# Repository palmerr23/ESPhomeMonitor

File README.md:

# ESPhomeMonitor
Hardware for monitoring equipment using HomeAssistant and Raspberry Pi Pico W-based ESPHome installation.

The boards described here are intended to be stacked, with the main Pico W board on top.

A 3D printable case is provided, with custom escutcheons for each input or output board type.

# Boards
+ Main: Pico W, 3 x peak reading analogue inputs (400mV - 48V), filtered PWM output.
+ Analog Input: 8 x analog inputs (3.5V - 48V) 3.81mm pluggable terminals or IDC connector.
+ Analog Input (RVR): A specialised analog input board for RVR TEX150 transmitters and TXRL/RXRL STL.
+ Digital Input: eight channels, opto-isolated or non-isolated. 3.81mm pluggable terminals or IDC connector.
+ Digital Output: eight channels, 4 x opto-isolated + 4 x relays, or non-isolated. 3.81mm pluggable terminals or IDC connector.
+ Expander Board: Second stack and additional 3.3V regulator.

The boards are designed in KiCAD. Gerbers and KiCAD source files are provided.

# Case
A modular, 3D printable case is provided.
+ Base with strain relief.
+ Mid section for additional input and output boards
+ Top section for main (Pico) board.

Each board type has a customised escutcheon panel that slots into the case, designed to be laser-cut from 2mm acrylic.

The case has a top panel with ventilation and mounting points for a SHT-40 I2C temperature and humidity sensor.

The case is joined together with 12mm tapped spacers and 15mm for the main Pico board.

Case files are in STL (body) or SVG (cover and escutcheons) format.

# Documentation and configuration 

+ Technical overview (HomeAssistant Monitoring and Control.pdf)

+ KiCAD design files and an example ESPHome configuration file for each board. 

+ HomeAssistant dashboard configuration is left to the constructor as needs will differ.

ESPHome and HomeAssistant documentation is regularly updated for both platforms:
https://www.home-assistant.io/
https://esphome.io/

The HomeAssistant community forum is a useful place to search for problem resolutions on both platforms.
https://community.home-assistant.io/

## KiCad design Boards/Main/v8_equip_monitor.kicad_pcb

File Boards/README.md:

# ESPhomeMonitor Boards

# Boards

+ Main: Pico W, 3 x peak reading analogue inputs (400mV - 48V), filtered PWM output.

+ Analog Input: 8 x analog inputs (3.5V - 48V) 3.81mm pluggable terminals or IDC connector.

+ Analog Input (RVR): A specialised analog input board for RVR TEX150 transmitters and TXRL/RXRL STL.

+ Digital Input: eight channels, opto-isolated or non-isolated. 3.81mm pluggable terminals or IDC connector.

+ Digital Output: eight channels, 4 x opto-isolated + 4 x relays, or non-isolated. 3.81mm pluggable terminals or IDC connector.

+ Expander Board: Second stack and additional 3.3V regulator.

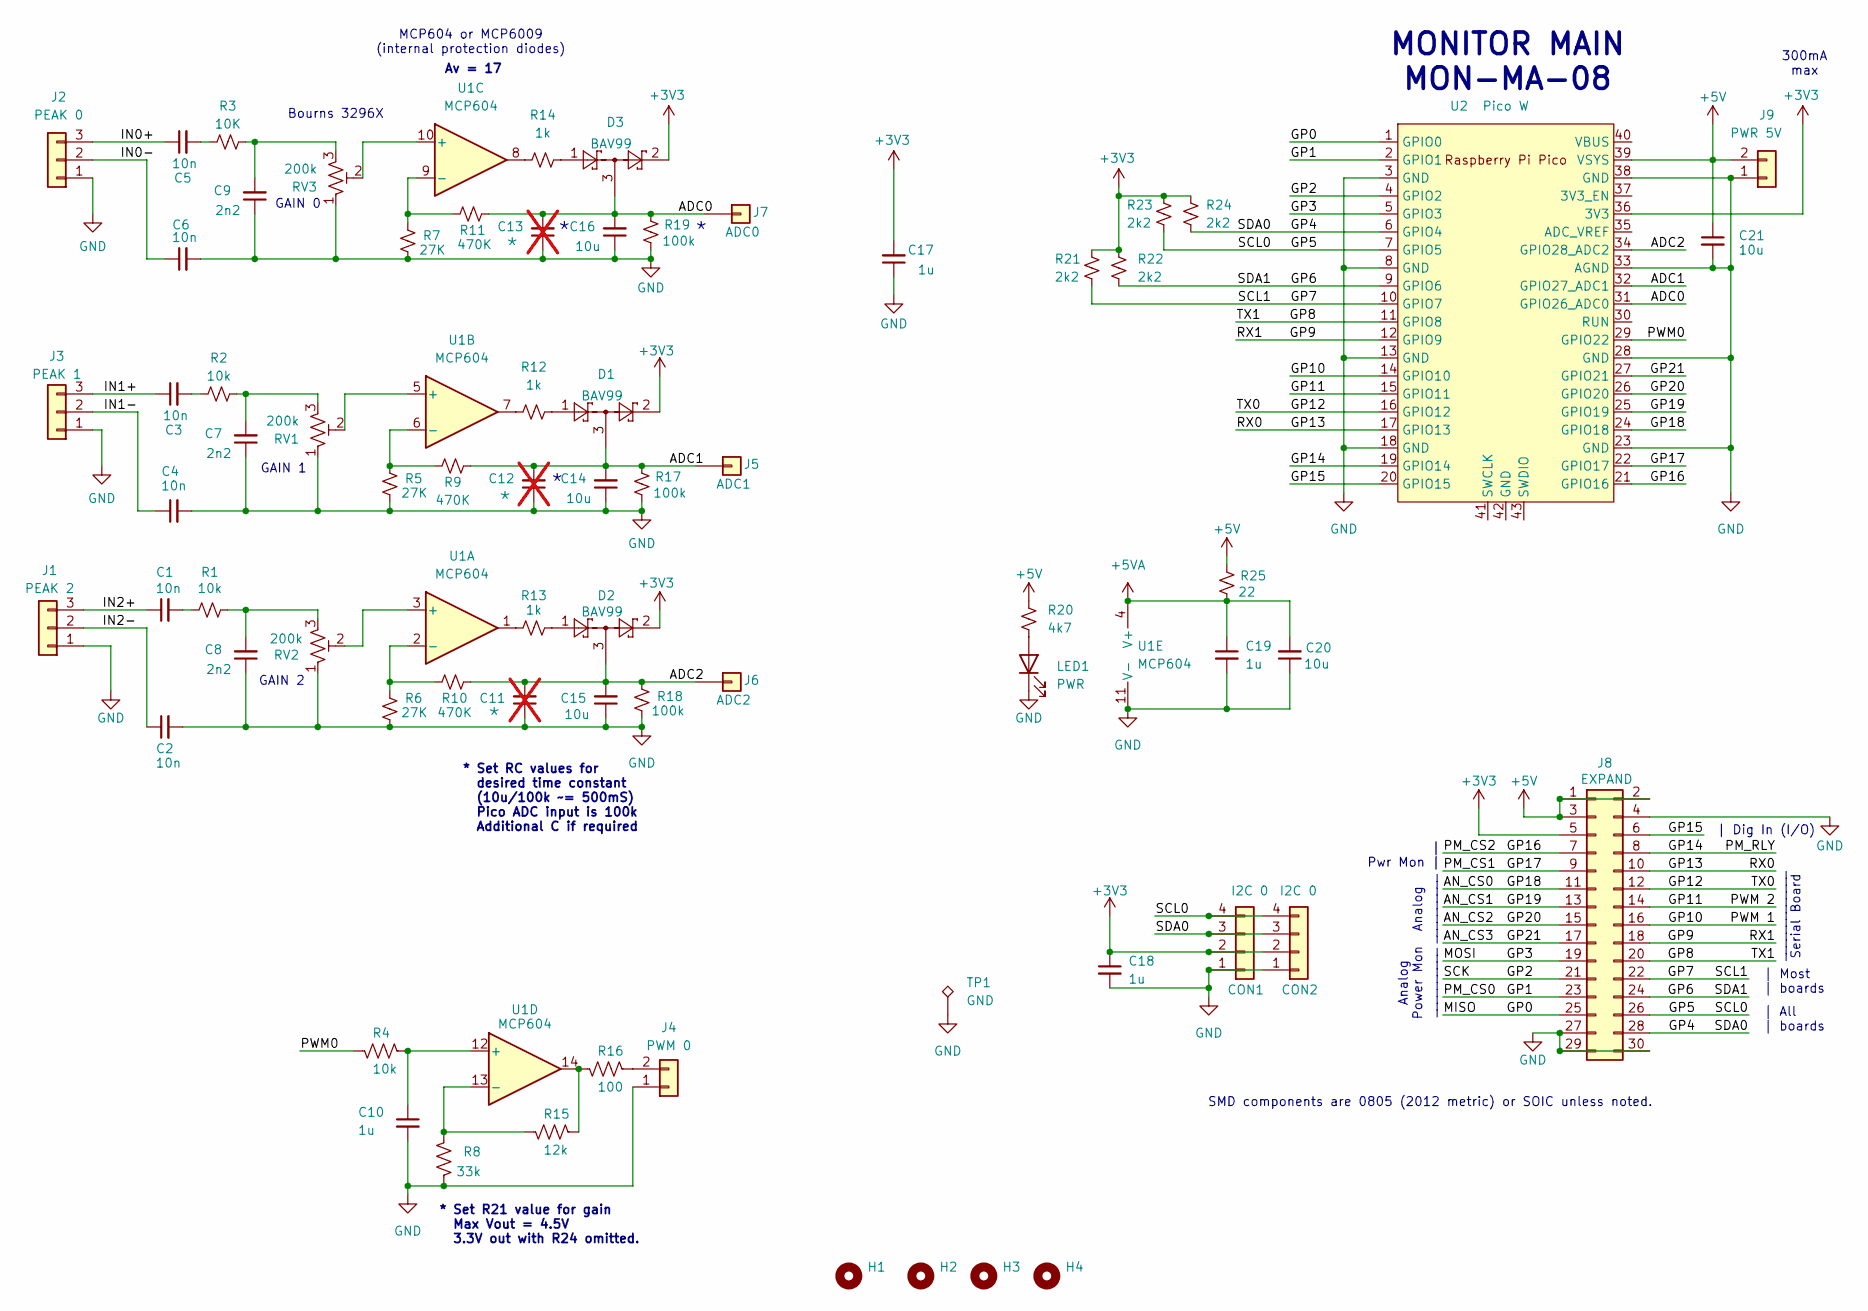
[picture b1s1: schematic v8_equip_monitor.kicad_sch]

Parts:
C1, C2, C3, C4, C5, C6: 10n; C_0805_2012Metric_Pad1.18x1.45mm_HandSolder
C7, C8, C9: 2n2; C_0805_2012Metric_Pad1.18x1.45mm_HandSolder
C10, C17, C18, C19: 1u; C_0805_2012Metric_Pad1.18x1.45mm_HandSolder
C11, C12, C13: *; C_0805_2012Metric_Pad1.18x1.45mm_HandSolder; not fitted
C14, C15, C16, C20, C21: 10u; C_0805_2012Metric_Pad1.18x1.45mm_HandSolder
CON1: I2C 0; PinSocket_1x04_P2.54mm_Vertical
CON2: I2C 0; JST_SH_SM04B-SRSS-TB_1x04-1MP_P1.00mm_Horizontal_wide_MP
D1, D2, D3: BAV99; SOT-23
H1, H2, H3, H4: MountingHole; MountingHole_3.5mm_no_fill
J1: PEAK 2; K3EDG; Mouser Part Number 649-220110-D031A01LF
J2: PEAK 0; K3EDG; Mouser Part Number 649-220110-D031A01LF
J3: PEAK 1; K3EDG; Mouser Part Number 649-220110-D031A01LF
J4: PWM 0; K2EDG; Mouser Part Number 649-220110-D021A01LF
J5: ADC1; PinHeader_1x01_P2.54mm_Vertical
J6: ADC2; PinHeader_1x01_P2.54mm_Vertical
J7: ADC0; PinHeader_1x01_P2.54mm_Vertical
J8: EXPAND; PinHeader_2x15_P2.54mm_Vertical
J9: PWR 5V; K2EDG
LED1: PWR; LED_0805_2012Metric_Pad1.15x1.40mm_HandSolder
R1, R2, R4: 10k; R_0805_2012Metric_Pad1.20x1.40mm_HandSolder
R3: 10K; R_0805_2012Metric_Pad1.20x1.40mm_HandSolder
R5, R6, R7: 27K; R_0805_2012Metric_Pad1.20x1.40mm_HandSolder
R8: 33k; R_0805_2012Metric_Pad1.20x1.40mm_HandSolder
R9, R10, R11: 470K; R_0805_2012Metric_Pad1.20x1.40mm_HandSolder
R12, R13, R14: 1k; R_0805_2012Metric_Pad1.20x1.40mm_HandSolder
R15: 12k; R_0805_2012Metric_Pad1.20x1.40mm_HandSolder
R16: 100; R_0805_2012Metric_Pad1.20x1.40mm_HandSolder
R17, R18, R19: 100k; R_0805_2012Metric_Pad1.20x1.40mm_HandSolder
R20: 4k7; R_0805_2012Metric_Pad1.20x1.40mm_HandSolder
R21, R22, R23, R24: 2k2; R_0805_2012Metric_Pad1.20x1.40mm_HandSolder
R25: 22; R_Axial_DIN0207_L6.3mm_D2.5mm_P10.16mm_Horizontal
RV1, RV2, RV3: 200k; Potentiometer_Bourns_3296X_Horizontal
TP1: GND; TestPoint_THTPad_2.0x2.0mm_Drill1.0mm
U1: MCP604; SOIC-14_3.9x8.7mm_P1.27mm
U2: Pico W; RPi_Pico_THT_BASIC_INSIDE

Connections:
+3V3: C17.2, C18.1, CON1.2, CON2.2, D1.2, D2.2, D3.2, J8.5, R21.1, R22.1, R23.1, R24.1, U2.36 (3V3)
+5V: C21.1, J8.1, J8.2, J8.3, J9.2, R20.1, R25.2, U2.39 (VSYS)
+5VA: C19.1, C20.2, R25.1, U1.4 (V+)
/ADC0: C13.2, C16.2, D3.3, J7.1, R11.2, R19.2, U2.31 (GPIO26_ADC0)
/ADC1: C12.2, C14.2, D1.3, J5.1, R9.2, R17.2, U2.32 (GPIO27_ADC1)
/ADC2: C11.2, C15.2, D2.3, J6.1, R10.2, R18.2, U2.34 (GPIO28_ADC2)
/AN_CS0: J8.11, U2.24 (GPIO18)
/AN_CS1: J8.13, U2.25 (GPIO19)
/AN_CS2: J8.15, U2.26 (GPIO20)
/AN_CS3: J8.17, U2.27 (GPIO21)
/GP0: J8.25, U2.1 (GPIO0)
/GP1: J8.23, U2.2 (GPIO1)
/GP2: J8.21, U2.4 (GPIO2)
/GP3: J8.19, U2.5 (GPIO3)
/GP4: CON1.3, CON2.3, J8.28, R24.2, U2.6 (GPIO4)
/GP5: CON1.4, CON2.4, J8.26, R23.2, U2.7 (GPIO5)
/GP6: J8.24, R22.2, U2.9 (GPIO6)
/GP7: J8.22, R21.2, U2.10 (GPIO7)
/GP8: J8.20, U2.11 (GPIO8)
/GP9: J8.18, U2.12 (GPIO9)
/GP10: J8.16, U2.14 (GPIO10)
/GP11: J8.14, U2.15 (GPIO11)
/GP12: J8.12, U2.16 (GPIO12)
/GP13: J8.10, U2.17 (GPIO13)
/GP14: J8.8, U2.19 (GPIO14)
/GP15: J8.6, U2.20 (GPIO15)
/GP16: J8.7, U2.21 (GPIO16)
/GP17: J8.9, U2.22 (GPIO17)
/IN0+: C5.1, J2.3
/IN0-: C6.1, J2.2
/IN1+: C3.1, J3.3
/IN1-: C4.1, J3.2
/IN2+: C1.1, J1.3
/IN2-: C2.1, J1.2
/PWM0: R4.1, U2.29 (GPIO22)
GND: C2.2, C4.2, C6.2, C7.1, C8.1, C9.1, C10.2, C11.1, C12.1, C13.1, C14.1, C15.1, C16.1, C17.1, C18.2, C19.2, C20.1, C21.2, CON1.1, CON2.1, J1.1, J2.1, J3.1, J4.1, J8.4, J8.27, J8.29, J8.30, J9.1, LED1.1 (K), R5.1, R6.1, R7.1, R8.1, R17.1, R18.1, R19.1, RV1.1, RV2.1, RV3.1, TP1.1, U1.11 (V-), U2.3 (GND), U2.8 (GND), U2.13 (GND), U2.18 (GND), U2.23 (GND), U2.28 (GND), U2.33 (AGND), U2.38 (GND)
unnamed: C1.2, R1.1
unnamed: C3.2, R2.1
unnamed: C5.2, R3.1
unnamed: C7.2, R2.2, RV1.3
unnamed: C8.2, R1.2, RV2.3
unnamed: C9.2, R3.2, RV3.3
unnamed: D1.1, R12.2
unnamed: D2.1, R13.2
unnamed: D3.1, R14.2
unnamed: J4.2, R16.2
unnamed: LED1.2 (A), R20.2
unnamed: R12.1, U1.7
unnamed: R13.1, U1.1
unnamed: R14.1, U1.8
unnamed: R15.2, R16.1, U1.14
unnamed: RV2.2, U1.3 (+)
unnamed: R6.2, R10.1, U1.2 (-)
unnamed: RV1.2, U1.5 (+)
unnamed: R5.2, R9.1, U1.6 (-)
unnamed: RV3.2, U1.10 (+)
unnamed: R7.2, R11.1, U1.9 (-)
unnamed: C10.1, R4.2, U1.12 (+)
unnamed: R8.2, R15.1, U1.13 (-)

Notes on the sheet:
Bourns 3296X
300mA max
| Pwr Mon |
| Dig In (I/O)
Analog Power Mon __________
* Set R21 value for gain Max Vout = 4.5V 3.3V out with R24 omitted.
GAIN 1
GAIN 2
MONITOR MAIN MON-MA-08
GAIN 0
Av = 17
| Most | boards
Analog __________
_____________ Serial Board
* Set RC values for desired time constant (10u/100k ~= 500mS) Pico ADC input is 100k Additional C if required
MCP604 or MCP6009 (internal protection diodes)
| All | boards
SMD components are 0805 (2012 metric) or SOIC unless noted.

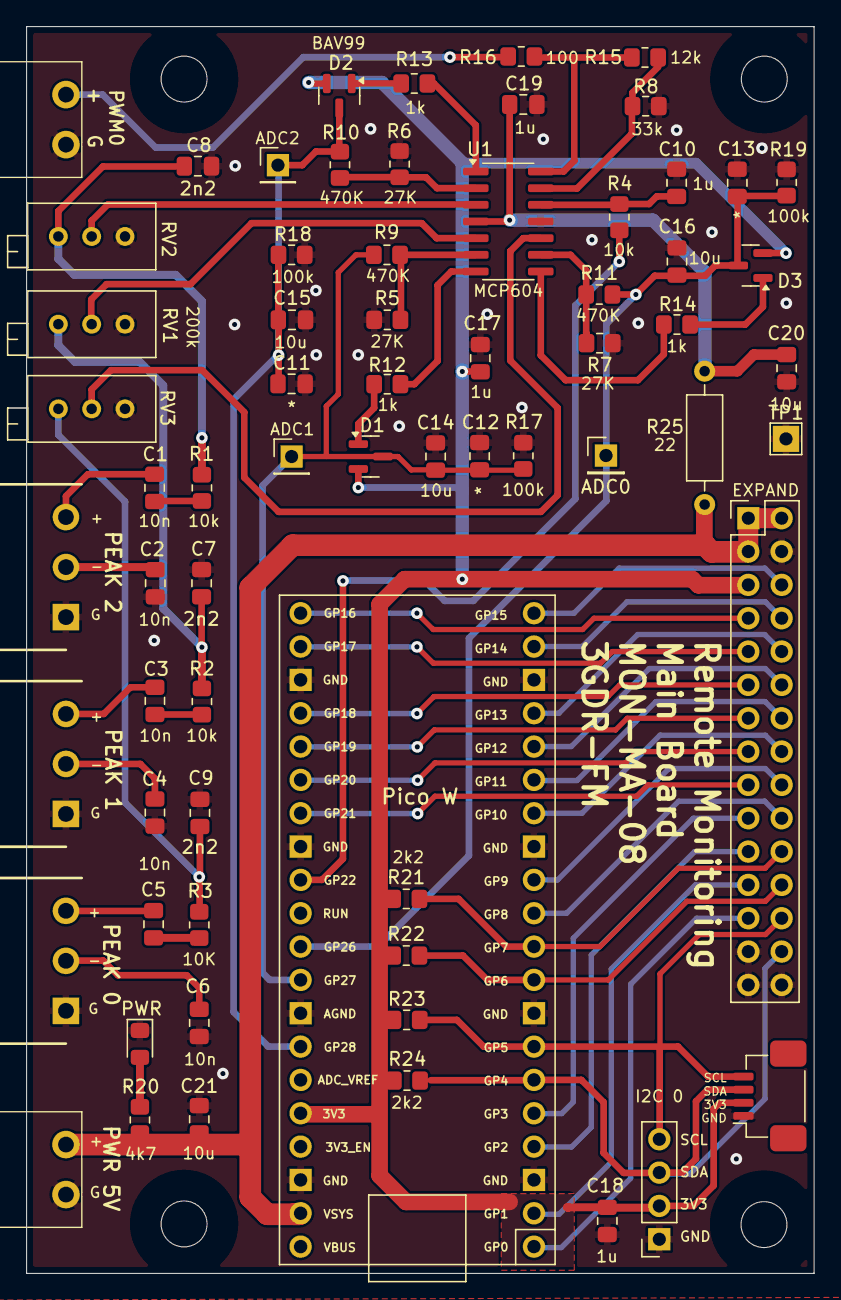
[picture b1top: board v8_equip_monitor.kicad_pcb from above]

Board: 2 copper layers, 60.0 x 95.0 mm, 71 parts (0 on the bottom side), 59 nets.

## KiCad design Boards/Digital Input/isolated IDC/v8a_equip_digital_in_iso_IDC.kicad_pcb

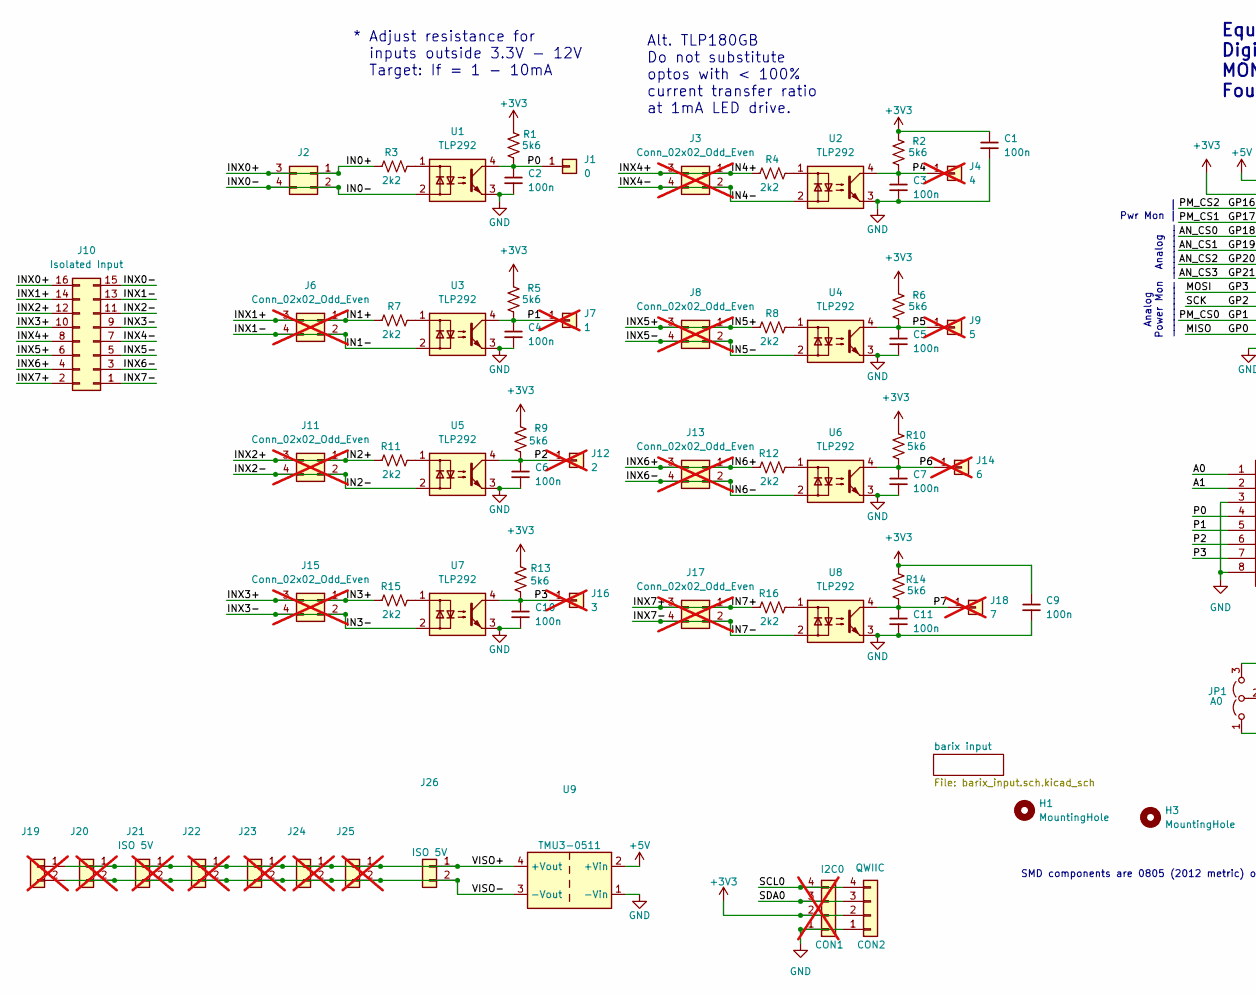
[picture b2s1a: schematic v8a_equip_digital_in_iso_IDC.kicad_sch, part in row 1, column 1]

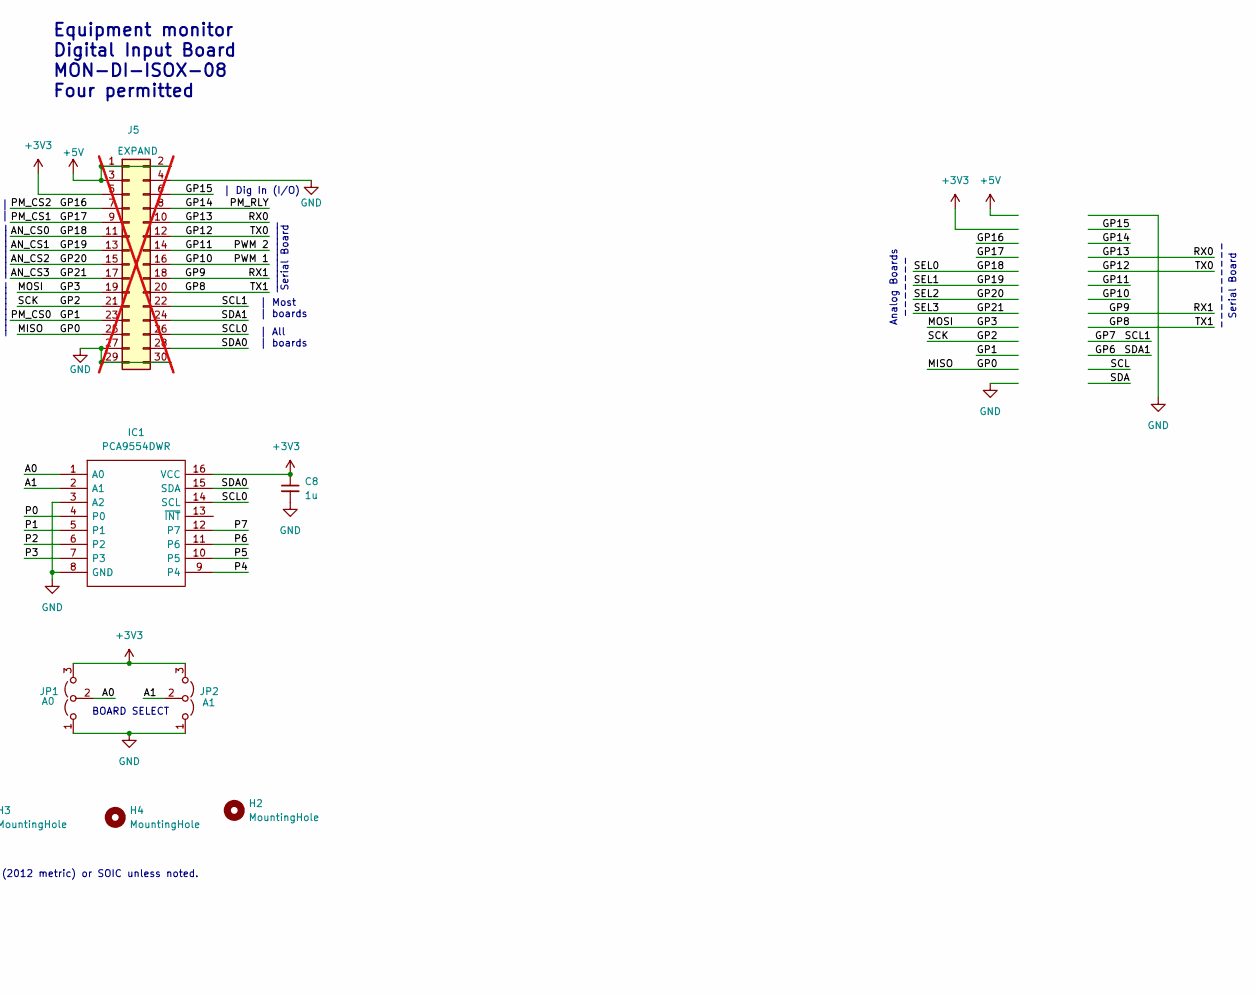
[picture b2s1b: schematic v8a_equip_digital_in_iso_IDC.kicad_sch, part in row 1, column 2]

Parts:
C1, C2, C3, C4, C5, C6, C7, C9, C10, C11: 100n; C_0805_2012Metric_Pad1.18x1.45mm_HandSolder
C8: 1u; C_0805_2012Metric_Pad1.18x1.45mm_HandSolder
CON1: I2C0; PinSocket_1x04_P2.54mm_Vertical; not fitted
CON2: QWIIC; JST_SH_SM04B-SRSS-TB_1x04-1MP_P1.00mm_Horizontal_wide_MP
H1, H2, H3, H4: MountingHole; MountingHole_3.5mm_no_fill
IC1: PCA9554DWR; SOIC127P1030X265-16N; Mouser Part Number 595-PCA9534DWR
J1: 0; PinHeader_1x01_P2.54mm_Vertical
J2: Conn_02x02_Odd_Even; PinHeader_2x02_P1.27mm_Vertical
J3, J6, J8, J11, J13, J15, J17: Conn_02x02_Odd_Even; PinHeader_2x02_P1.27mm_Vertical; not fitted
J4: 4; PinHeader_1x01_P2.54mm_Vertical; not fitted
J5: EXPAND; PinHeader_2x15_P2.54mm_Vertical; not fitted
J7: 1; PinHeader_1x01_P2.54mm_Vertical; not fitted
J9: 5; PinHeader_1x01_P2.54mm_Vertical; not fitted
J10: Isolated Input; SHDRRA16W63P254_2X8_2290X1740X700P; Mouser Part Number 538-90130-3112
J12: 2; PinHeader_1x01_P2.54mm_Vertical; not fitted
J14: 6; PinHeader_1x01_P2.54mm_Vertical; not fitted
J16: 3; PinHeader_1x01_P2.54mm_Vertical; not fitted
J18: 7; PinHeader_1x01_P2.54mm_Vertical; not fitted
J19, J20, J22, J23, J24, J25: Conn_02x02_Odd_Even; PinHeader_1x02_P1.27mm_Vertical; not fitted
J21: ISO 5V; PinHeader_1x02_P1.27mm_Vertical; not fitted
J26: ISO 5V; PinHeader_1x02_P1.27mm_Vertical
JP1: A0; PinHeader_1x03_P2.54mm_Vertical
JP2: A1; PinHeader_1x03_P2.54mm_Vertical
R1, R2, R5, R6, R9, R10, R13, R14: 5k6; R_0805_2012Metric_Pad1.20x1.40mm_HandSolder
R3, R4, R7, R8, R11, R12, R15, R16: 2k2; R_0805_2012Metric_Pad1.20x1.40mm_HandSolder
U1, U2, U3, U4, U5, U6, U7, U8: TLP292; TLP_OPTO_WIDE_PINS
U9: TMU3-0511; Converter_DCDC_TRACO_TMU3-05xx_12xx_THT

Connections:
+3V3: C1.1, C8.1, C9.1, CON1.2, CON2.2, IC1.16 (VCC), J5.5, JP1.3 (B), JP2.3 (B), R1.1, R2.1, R5.1, R6.1, R9.1, R10.1, R13.1, R14.1
+5V: J5.1, J5.2, J5.3, U9.2 (+Vin)
/A0: IC1.1 (A0), JP1.2 (C)
/A1: IC1.2 (A1), JP2.2 (C)
/AN_CS0: J5.11
/AN_CS1: J5.13
/AN_CS2: J5.15
/AN_CS3: J5.17
/GP0: J5.25
/GP1: J5.23
/GP2: J5.21
/GP3: J5.19
/GP6: J5.24
/GP7: J5.22
/GP8: J5.20
/GP9: J5.18
/GP10: J5.16
/GP11: J5.14
/GP12: J5.12
/GP13: J5.10
/GP14: J5.8
/GP15: J5.6
/GP16: J5.7
/GP17: J5.9
/IN0+: J2.1, J2.3, J10.16, R3.2
/IN0-: J2.2, J2.4, J10.15, U1.2
/IN1+: J6.1, J6.3, J10.14, R7.2
/IN1-: J6.2, J6.4, J10.13, U3.2
/IN2+: J10.12, J11.1, J11.3, R11.2
/IN2-: J10.11, J11.2, J11.4, U5.2
/IN3+: J10.10, J15.1, J15.3, R15.2
/IN3-: J10.9, J15.2, J15.4, U7.2
/IN4+: J3.1, J3.3, J10.8, R4.2
/IN4-: J3.2, J3.4, J10.7, U2.2
/IN5+: J8.1, J8.3, J10.6, R8.2
/IN5-: J8.2, J8.4, J10.5, U4.2
/IN6+: J10.4, J13.1, J13.3, R12.2
/IN6-: J10.3, J13.2, J13.4, U6.2
/IN7+: J10.2, J17.1, J17.3, R16.2
/IN7-: J10.1, J17.2, J17.4, U8.2
/P0: C2.1, IC1.4 (P0), J1.1, R1.2, U1.4
/P1: C4.1, IC1.5 (P1), J7.1, R5.2, U3.4
/P2: C6.1, IC1.6 (P2), J12.1, R9.2, U5.4
/P3: C10.1, IC1.7 (P3), J16.1, R13.2, U7.4
/P4: C3.1, IC1.9 (P4), J4.1, R2.2, U2.4
/P5: C5.1, IC1.10 (P5), J9.1, R6.2, U4.4
/P6: C7.1, IC1.11 (P6), J14.1, R10.2, U6.4
/P7: C11.1, IC1.12 (P7), J18.1, R14.2, U8.4
/SCL0: CON1.4, CON2.4, IC1.14 (SCL), J5.26
/SDA0: CON1.3, CON2.3, IC1.15 (SDA), J5.28
/VISO+: J19.1, J20.1, J21.1, J22.1, J23.1, J24.1, J25.1, J26.1, U9.4 (+Vout)
/VISO-: J19.2, J20.2, J21.2, J22.2, J23.2, J24.2, J25.2, J26.2, U9.3 (-Vout)
GND: C1.2, C2.2, C3.2, C4.2, C5.2, C6.2, C7.2, C8.2, C9.2, C10.2, C11.2, CON1.1, CON2.1, IC1.3 (A2), IC1.8 (GND), J5.4, J5.27, J5.29, J5.30, JP1.1 (A), JP2.1 (A), U1.3, U2.3, U3.3, U4.3, U5.3, U6.3, U7.3, U8.3, U9.1 (-Vin)
unnamed: R3.1, U1.1
unnamed: R4.1, U2.1
unnamed: R7.1, U3.1
unnamed: R8.1, U4.1
unnamed: R11.1, U5.1
unnamed: R12.1, U6.1
unnamed: R15.1, U7.1
unnamed: R16.1, U8.1

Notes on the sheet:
| Pwr Mon |
Analog __________
BOARD SELECT
SMD components are 0805 (2012 metric) or SOIC unless noted.
| Dig In (I/O)
_____________ Serial Board
---------- Serial Board
Equipment monitor Digital Input Board MON-DI-ISOX-08 Four permitted
Analog Power Mon __________
| All | boards
* Adjust resistance for inputs outside 3.3V - 12V Target: If = 1 - 10mA
| Most | boards
Alt. TLP180GB Do not substitute optos with < 100% current transfer ratio at 1mA LED drive.
Analog Boards -------

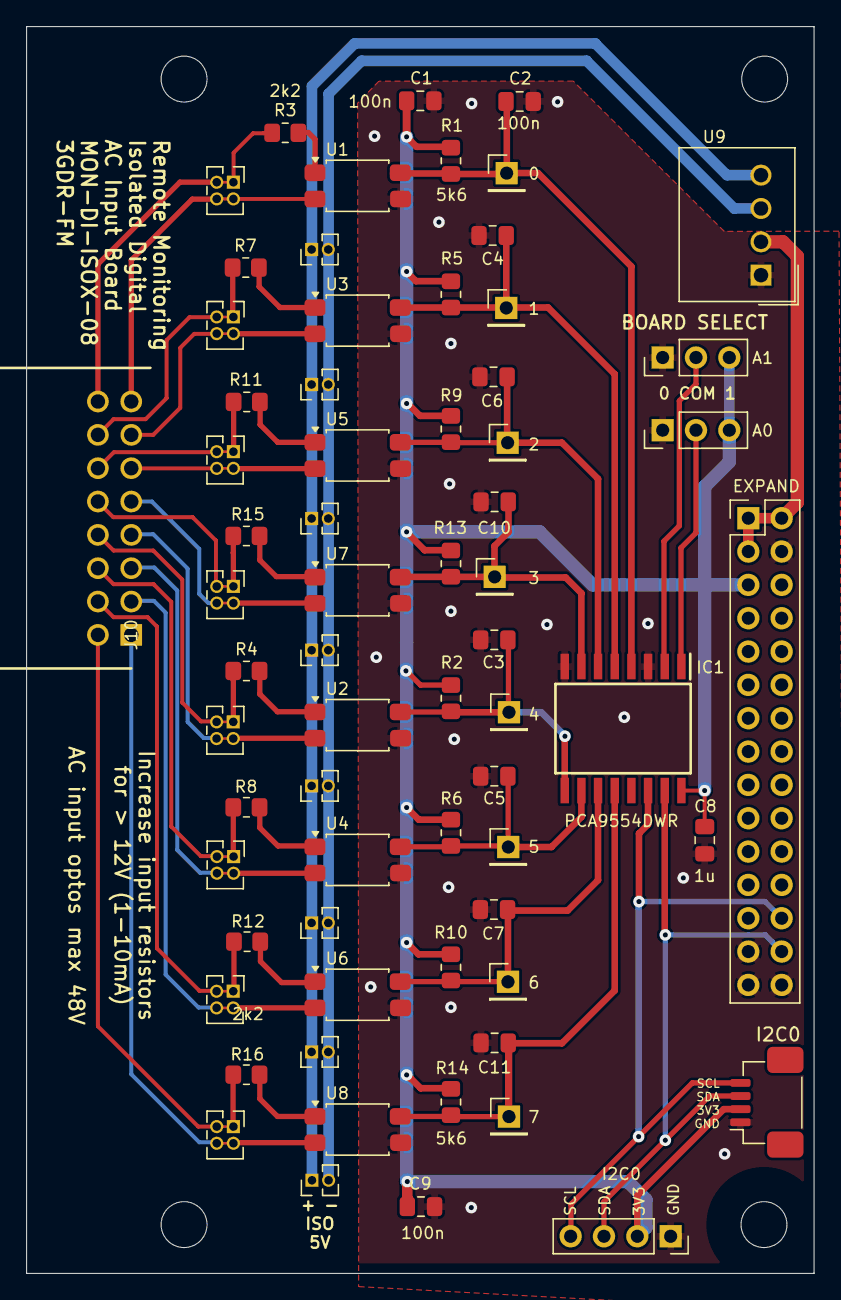
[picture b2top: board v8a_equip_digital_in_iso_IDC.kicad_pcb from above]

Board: 2 copper layers, 60.0 x 95.0 mm, 71 parts (0 on the bottom side), 41 nets.

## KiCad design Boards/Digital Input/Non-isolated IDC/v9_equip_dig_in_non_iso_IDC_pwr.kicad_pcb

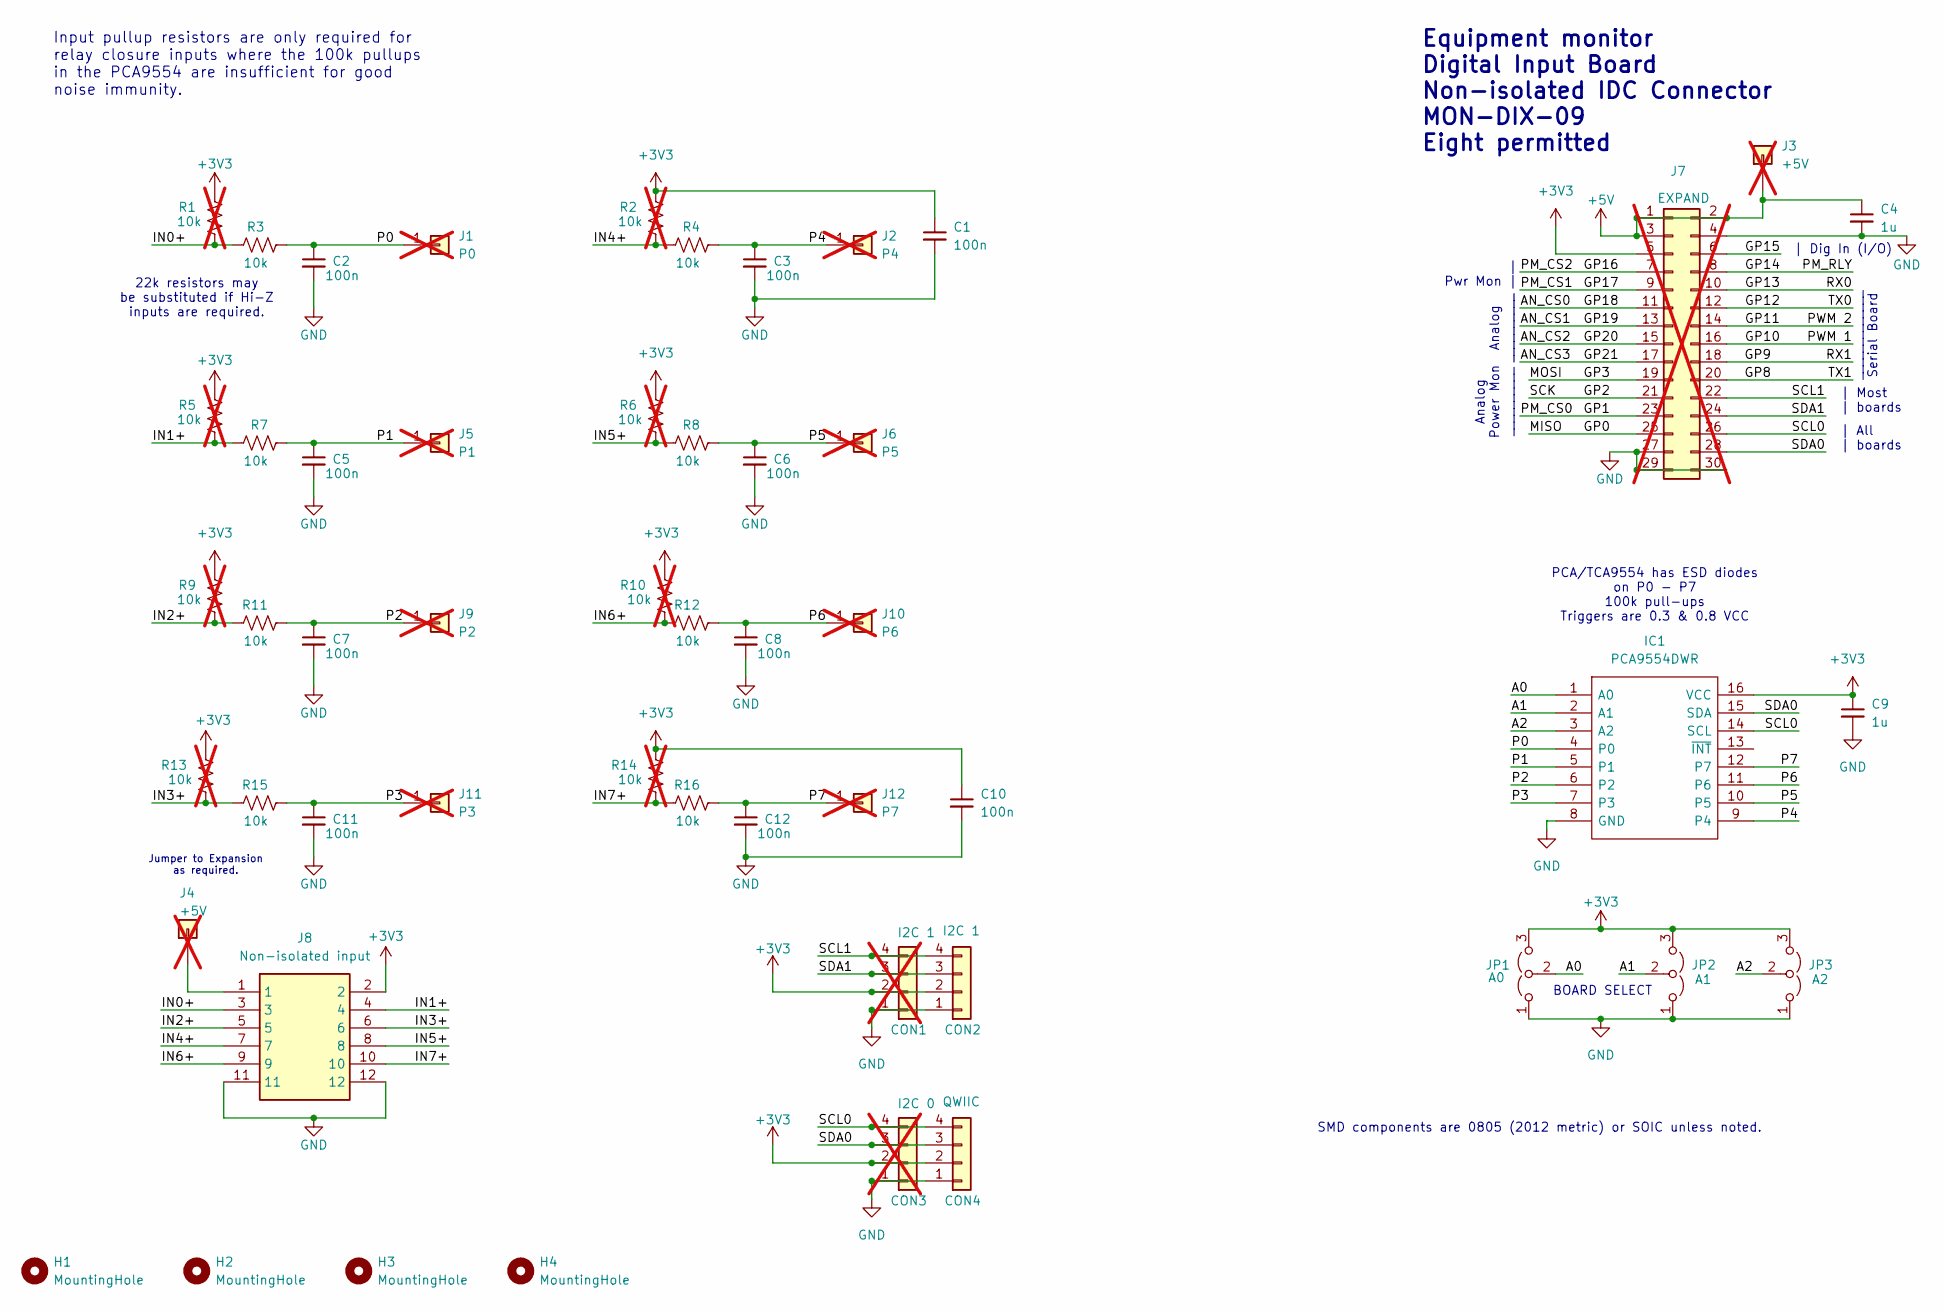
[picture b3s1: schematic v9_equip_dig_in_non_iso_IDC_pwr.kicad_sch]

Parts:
C1, C2, C3, C5, C6, C7, C8, C10, C11, C12: 100n; C_0805_2012Metric_Pad1.18x1.45mm_HandSolder
C4, C9: 1u; C_0805_2012Metric_Pad1.18x1.45mm_HandSolder
CON1: I2C 1; PinSocket_1x04_P2.54mm_Vertical; not fitted
CON2: I2C 1; JST_SH_SM04B-SRSS-TB_1x04-1MP_P1.00mm_Horizontal_wide_MP
CON3: I2C 0; PinSocket_1x04_P2.54mm_Vertical; not fitted
CON4: QWIIC; JST_SH_SM04B-SRSS-TB_1x04-1MP_P1.00mm_Horizontal_wide_MP
H1, H2, H3, H4: MountingHole; MountingHole_3.5mm_no_fill
IC1: PCA9554DWR; SOIC127P1030X265-16N; Mouser Part Number 595-PCA9534DWR
J1: P0; PinHeader_1x01_P2.54mm_Vertical; not fitted
J2: P4; PinHeader_1x01_P2.54mm_Vertical; not fitted
J3, J4: +5V; PinHeader_1x01_P2.54mm_Vertical; not fitted
J5: P1; PinHeader_1x01_P2.54mm_Vertical; not fitted
J6: P5; PinHeader_1x01_P2.54mm_Vertical; not fitted
J7: EXPAND; PinHeader_2x15_P2.54mm_Vertical; not fitted
J8: Non-isolated input; SHDRRA12W65P254_2X6_1758X1090X1005P; Mouser Part Number 538-90130-3112
J9: P2; PinHeader_1x01_P2.54mm_Vertical; not fitted
J10: P6; PinHeader_1x01_P2.54mm_Vertical; not fitted
J11: P3; PinHeader_1x01_P2.54mm_Vertical; not fitted
J12: P7; PinHeader_1x01_P2.54mm_Vertical; not fitted
JP1: A0; PinHeader_1x03_P2.54mm_Vertical
JP2: A1; PinHeader_1x03_P2.54mm_Vertical
JP3: A2; PinHeader_1x03_P2.54mm_Vertical
R1, R2, R5, R6, R9, R10, R13, R14: 10k; R_0805_2012Metric_Pad1.20x1.40mm_HandSolder; not fitted
R3, R4, R7, R8, R11, R12, R15, R16: 10k; R_0805_2012Metric_Pad1.20x1.40mm_HandSolder

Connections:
+3V3: C1.1, C9.1, C10.1, CON1.2, CON2.2, CON3.2, CON4.2, IC1.16 (VCC), J7.5, J8.2, JP1.3 (B), JP2.3 (B), JP3.3 (B), R1.1, R2.1, R5.1, R6.1, R9.1, R10.1, R13.1, R14.1
+5V: C4.1, J3.1, J7.1, J7.2, J7.3
/A0: IC1.1 (A0), JP1.2 (C)
/A1: IC1.2 (A1), JP2.2 (C)
/A2: IC1.3 (A2), JP3.2 (C)
/AN_CS0: J7.11
/AN_CS1: J7.13
/AN_CS2: J7.15
/AN_CS3: J7.17
/GP0: J7.25
/GP1: J7.23
/GP2: J7.21
/GP3: J7.19
/GP8: J7.20
/GP9: J7.18
/GP10: J7.16
/GP11: J7.14
/GP12: J7.12
/GP13: J7.10
/GP14: J7.8
/GP15: J7.6
/GP16: J7.7
/GP17: J7.9
/IN0+: J8.3, R1.2, R3.2
/IN1+: J8.4, R5.2, R7.2
/IN2+: J8.5, R9.2, R11.2
/IN3+: J8.6, R13.2, R15.2
/IN4+: J8.7, R2.2, R4.2
/IN5+: J8.8, R6.2, R8.2
/IN6+: J8.9, R10.2, R12.2
/IN7+: J8.10, R14.2, R16.2
/P0: C2.1, IC1.4 (P0), J1.1, R3.1
/P1: C5.1, IC1.5 (P1), J5.1, R7.1
/P2: C7.1, IC1.6 (P2), J9.1, R11.1
/P3: C11.1, IC1.7 (P3), J11.1, R15.1
/P4: C3.1, IC1.9 (P4), J2.1, R4.1
/P5: C6.1, IC1.10 (P5), J6.1, R8.1
/P6: C8.1, IC1.11 (P6), J10.1, R12.1
/P7: C12.1, IC1.12 (P7), J12.1, R16.1
/SCL0: CON3.4, CON4.4, IC1.14 (SCL), J7.26
/SCL1: CON1.4, CON2.4, J7.22
/SDA0: CON3.3, CON4.3, IC1.15 (SDA), J7.28
/SDA1: CON1.3, CON2.3, J7.24
GND: C1.2, C2.2, C3.2, C4.2, C5.2, C6.2, C7.2, C8.2, C9.2, C10.2, C11.2, C12.2, CON1.1, CON2.1, CON3.1, CON4.1, IC1.8 (GND), J7.4, J7.27, J7.29, J7.30, J8.11, J8.12, JP1.1 (A), JP2.1 (A), JP3.1 (A)
unnamed: J4.1, J8.1

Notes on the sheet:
PCA/TCA9554 has ESD diodes on P0 - P7 100k pull-ups Triggers are 0.3 & 0.8 VCC
| Pwr Mon |
Analog __________
22k resistors may be substituted if Hi-Z inputs are required.
BOARD SELECT
SMD components are 0805 (2012 metric) or SOIC unless noted.
| Dig In (I/O)
_____________ Serial Board
Equipment monitor Digital Input Board Non-isolated IDC Connector MON-DIX-09 Eight permitted
Analog Power Mon __________
| All | boards
Jumper to Expansion as required.
Input pullup resistors are only required for relay closure inputs where the 100k pullups in the PCA9554 are insufficient for good noise immunity.
| Most | boards

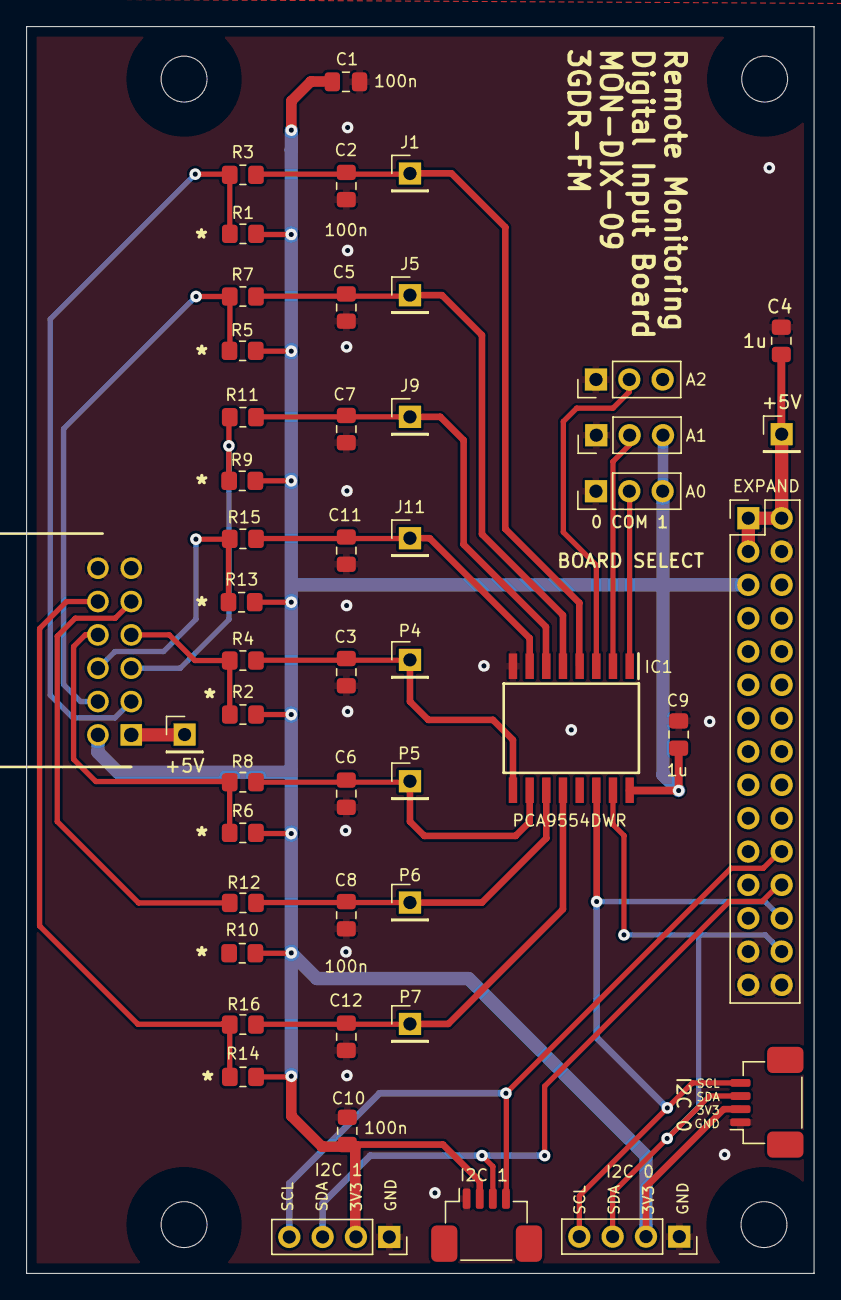
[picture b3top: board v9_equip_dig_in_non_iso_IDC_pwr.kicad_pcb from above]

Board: 2 copper layers, 60.0 x 95.0 mm, 52 parts (0 on the bottom side), 27 nets.

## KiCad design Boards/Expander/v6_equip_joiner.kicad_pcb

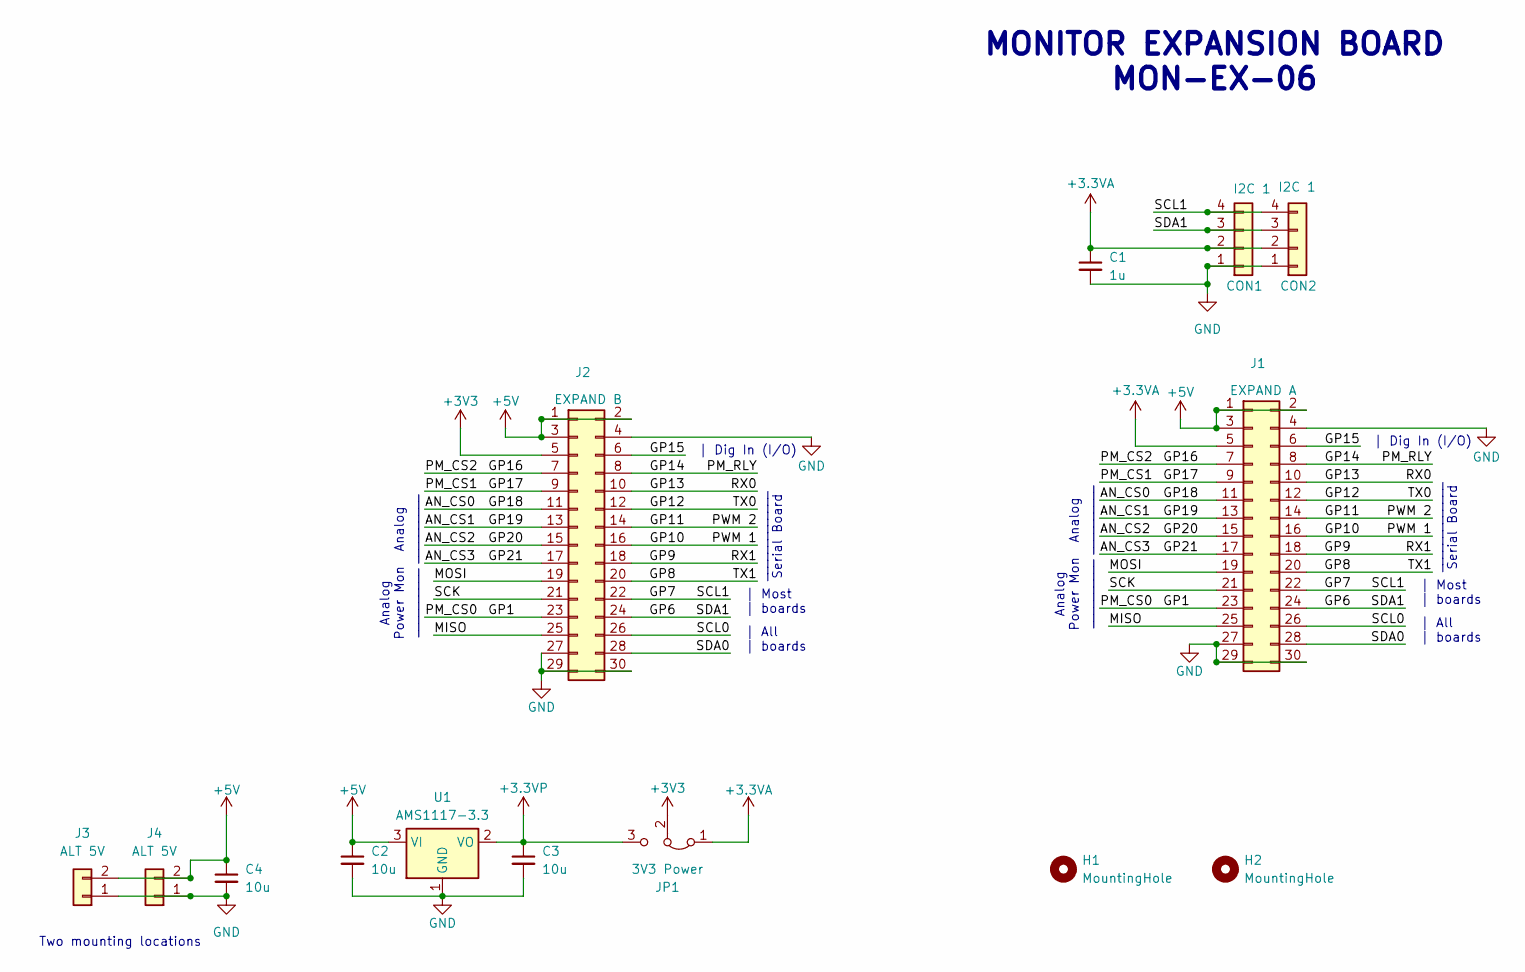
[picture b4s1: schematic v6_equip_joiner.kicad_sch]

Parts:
C1: 1u; C_0805_2012Metric_Pad1.18x1.45mm_HandSolder
C2, C3, C4: 10u; C_0805_2012Metric_Pad1.18x1.45mm_HandSolder
CON1: I2C 1; PinSocket_1x04_P2.54mm_Vertical
CON2: I2C 1; JST_SH_SM04B-SRSS-TB_1x04-1MP_P1.00mm_Horizontal_wide_MP
H1, H2: MountingHole; MountingHole_3.5mm
J1: EXPAND A; PinHeader_2x15_P2.54mm_Vertical
J2: EXPAND B; PinHeader_2x15_P2.54mm_Vertical
J3, J4: ALT 5V; OQ0232510000G
JP1: 3V3 Power; SolderJumper-3_P1.3mm_Bridged12_Pad1.5x1.5mm_NumberLabels
U1: AMS1117-3.3; SOT-223-3_TabPin2

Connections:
+3.3VA: C1.1, CON1.2, CON2.2, J1.5, JP1.1 (A)
+3.3VP: C3.1, JP1.3 (B), U1.2 (VO)
+3V3: J2.5, JP1.2 (C)
+5V: C2.1, C4.1, J1.1, J1.2, J1.3, J2.1, J2.2, J2.3, J3.2, J4.2, U1.3 (VI)
/AN_CS0: J1.11, J2.11
/AN_CS1: J1.13, J2.13
/AN_CS2: J1.15, J2.15
/AN_CS3: J1.17, J2.17
/GP1: J1.23, J2.23
/GP6: CON1.3, CON2.3, J1.24, J2.24
/GP7: CON1.4, CON2.4, J1.22, J2.22
/GP8: J1.20, J2.20
/GP9: J1.18, J2.18
/GP10: J1.16, J2.16
/GP11: J1.14, J2.14
/GP12: J1.12, J2.12
/GP13: J1.10, J2.10
/GP14: J1.8, J2.8
/GP15: J1.6, J2.6
/GP16: J1.7, J2.7
/GP17: J1.9, J2.9
/MISO: J1.25, J2.25
/MOSI: J1.19, J2.19
/SCK: J1.21, J2.21
/SCL0: J1.26, J2.26
/SDA0: J1.28, J2.28
GND: C1.2, C2.2, C3.2, C4.2, CON1.1, CON2.1, J1.4, J1.27, J1.29, J1.30, J2.4, J2.27, J2.29, J2.30, J3.1, J4.1, U1.1 (GND)

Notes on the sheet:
| All | boards
| Dig In (I/O)
_____________ Serial Board
Analog __________
| Most | boards
Analog Power Mon __________
MONITOR EXPANSION BOARD MON-EX-06
Two mounting locations

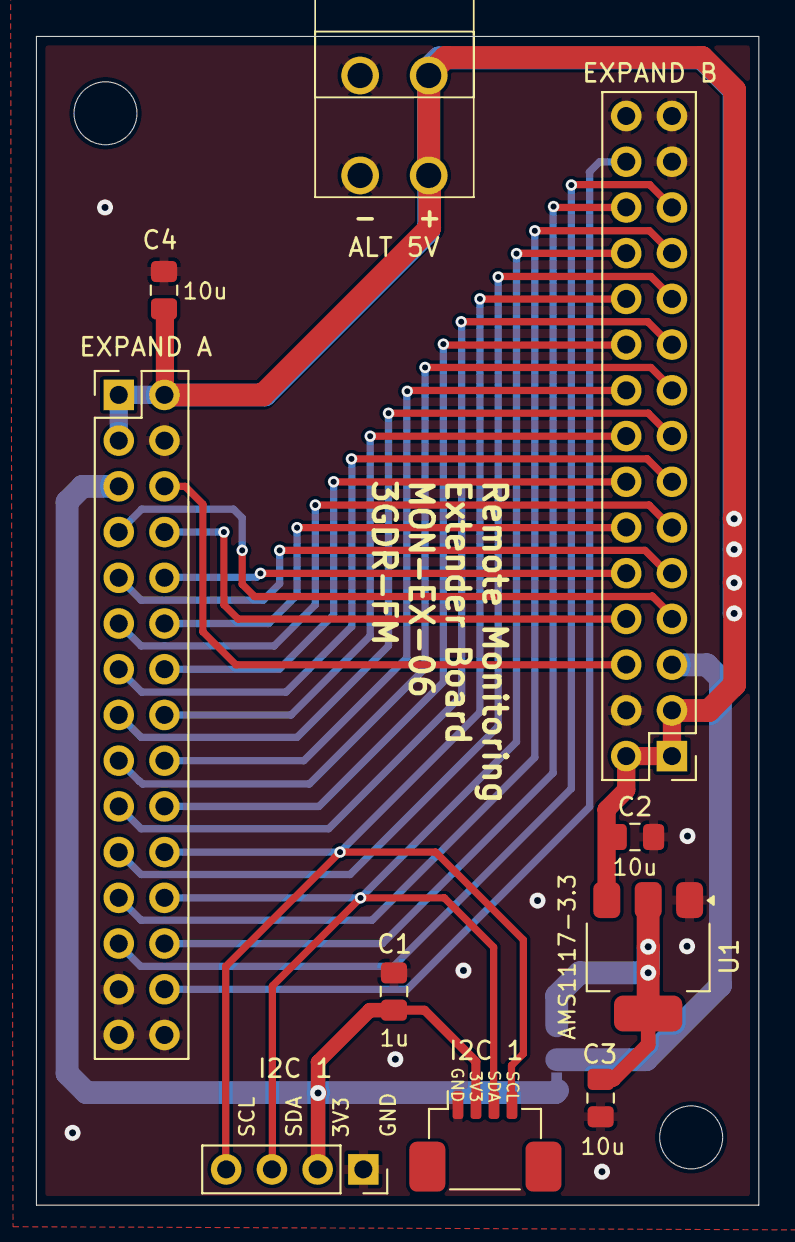
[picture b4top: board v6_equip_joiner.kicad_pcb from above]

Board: 2 copper layers, 40.1 x 64.9 mm, 14 parts (1 on the bottom side), 27 nets.
